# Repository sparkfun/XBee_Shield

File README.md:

XBee Shield
===========

<table class="table table-hover table-striped table-bordered">
  <tr align="center">
   <td></td>
   <td></td>
  </tr>
  <tr align="center">
    <td>XBee Shield [<a href="https://www.sparkfun.com/products/12847">WRL-12847</a>]</td>
    <td>SparkFun XBee Wireless Kit [<a href="https://www.sparkfun.com/products/13197">KIT-13197</a>]</td>
  </tr>
</table>

This shield mates directly with any dev board that has an Arduino standard footprint and equips it with the wireless
communication capabilities using the popular XBee modules. 

Repository Contents
-------------------
* **/Hardware** - All Eagle design files (.brd, .sch)
* **/Production** - Test bed files and production panel files

Documentation
--------------
* **[Exploring XBees and XCTU](https://learn.sparkfun.com/tutorials/exploring-xbees-and-xctu)** - Getting started with the XBee software and configuring XBees.
* **[Hookup Guide](https://learn.sparkfun.com/tutorials/xbee-shield-hookup-guide)** - Basic hookup guide for the XBee Shield for Arduinos.

Product Versions
----------------
* [WRL-12847](https://www.sparkfun.com/products/12847)- XBee Shield
* [KIT-13197](https://www.sparkfun.com/products/13197)- XBee Wireless Kit with XBee Series 1 Modules

Version History
---------------
* [v14](https://www.sparkfun.com/products/10854) Version 1.4. 

License Information
-------------------
License Information
-------------------

This product is _**open source**_! 

Please review the LICENSE.md file for license information. 

If you have any questions or concerns on licensing, please contact techsupport@sparkfun.com.

Distributed as-is; no warranty is given.

- Your friends at SparkFun.

_<COLLABORATION CREDIT>_

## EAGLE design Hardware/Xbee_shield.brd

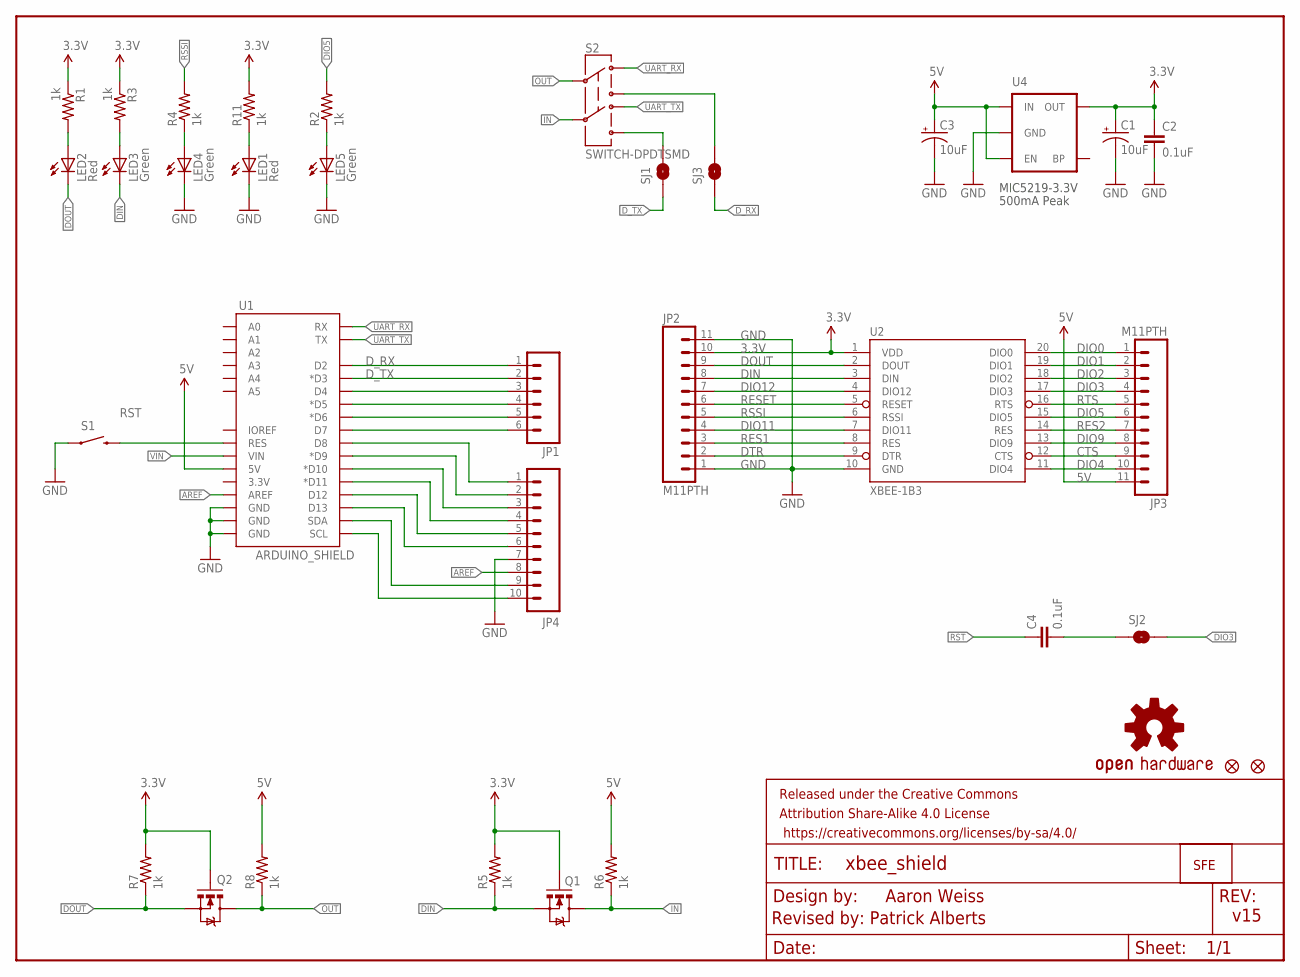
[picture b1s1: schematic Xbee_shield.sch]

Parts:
C1, C3: 10uF; EIA3216
C2, C4: 0.1uF; 0603-CAP
FRAME1: FRAME-LETTER; CREATIVE_COMMONS
JP1: M06SIP; 1X06
JP2, JP3: M11PTH; 1X11
JP4: M10"; 1X10
JP5, JP6: FIDUCIAL1X2; FIDUCIAL-1X2
JP7: LOGO-SFENEW; SFE-NEW-WEBLOGO
LED1, LED2: Red; LED-0603
LED3, LED4, LED5: Green; LED-0603
Q1, Q2: MOSFET-NCHANNELSMD; SOT23-3
R1, R2, R3, R4, R5, R6, R7, R8, R11: 1k; 0603-RES
S1: SWITCH-MOMENTARY-2SMD; TACTILE_SWITCH_SMD
S2: SWITCH-DPDTSMD; AYZ0202
SJ1: D_TX; SJ_2S
SJ2: SOLDERJUMPERTRACE; SJ_2S-TRACE
SJ3: D_RX; SJ_2S
U1: ARDUINO_SHIELD; UNO_R3_SHIELD
U2: XBEE-1B3; XBEE-SMD
U4: V_REG_LDOSMD; SOT23-5
U$8: OSHW-LOGOS; OSHW-LOGO-S

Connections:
3.3V: C1.A (+), C2.1, JP2.10, Q1.1 (G), Q2.1 (G), R1.1, R3.1, R5.2, R7.2, R11.2, U2.1 (VDD), U4.5 (OUT)
5V: C3.A (+), JP3.11, R6.2, R8.2, U1.5V, U4.1 (IN), U4.3 (EN)
AREF: JP4.8, U1.AREF
CTS: JP3.9, U2.12 (CTS)
DIN: JP2.8, LED3.C, Q1.2 (S), R5.1, U2.3 (DIN)
DIO0: JP3.1, U2.20 (DIO0)
DIO1: JP3.2, U2.19 (DIO1)
DIO2: JP3.3, U2.18 (DIO2)
DIO3: JP3.4, SJ2.2, U2.17 (DIO3)
DIO4: JP3.10, U2.11 (DIO4)
DIO5: JP3.6, R2.2, U2.15 (DIO5)
DIO9: JP3.8, U2.13 (DIO9)
DIO11: JP2.4, U2.7 (DIO11)
DIO12: JP2.7, U2.4 (DIO12)
DOUT: JP2.9, LED2.C, Q2.2 (S), R7.1, U2.2 (DOUT)
DTR: JP2.2, U2.9 (DTR)
D_RX: JP1.1, SJ3.1, U1.D2
D_TX: JP1.2, SJ1.1, U1.D3 (*D3)
GND: C1.C (-), C2.2, C3.C (-), JP2.1, JP2.11, JP4.7, LED1.C, LED4.C, LED5.C, S1.1, U1.GND@0 (GND), U1.GND@1 (GND), U1.GND@2 (GND), U2.10 (GND), U4.2 (GND)
IN: Q1.3 (D), R6.1, S2.5
unnamed: LED2.A, R1.2
unnamed: LED4.A, R4.1
unnamed: JP4.6, U1.D13
unnamed: LED3.A, R3.2
unnamed: C4.2, SJ2.1
unnamed: JP4.9, U1.SDA
unnamed: JP4.10, U1.SCL
unnamed: JP4.1, U1.D8
unnamed: JP4.2, U1.D9 (*D9)
unnamed: JP4.3, U1.D10 (*D10)
unnamed: LED1.A, R11.1
unnamed: JP4.4, U1.D11 (*D11)
unnamed: JP4.5, U1.D12
unnamed: LED5.A, R2.1
unnamed: S2.6, SJ1.2
unnamed: S2.3, SJ3.2
unnamed: JP1.3, U1.D4
unnamed: JP1.4, U1.D5 (*D5)
unnamed: JP1.5, U1.D6 (*D6)
unnamed: JP1.6, U1.D7
OUT: Q2.3 (D), R8.1, S2.2
RES1: JP2.3, U2.8 (RES)
RES2: JP3.7, U2.14 (RES)
RESET: JP2.6, U2.5 (RESET)
RSSI: JP2.5, R4.2, U2.6 (RSSI)
RST: C4.1, S1.3 (2), U1.RES
RTS: JP3.5, U2.16 (RTS)
UART_RX: S2.1, U1.RX
UART_TX: S2.4, U1.TX
VIN: U1.VIN

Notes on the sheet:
500mA Peak
MIC5219-3.3V
Aaron Weiss
v15
Revised by: Patrick Alberts

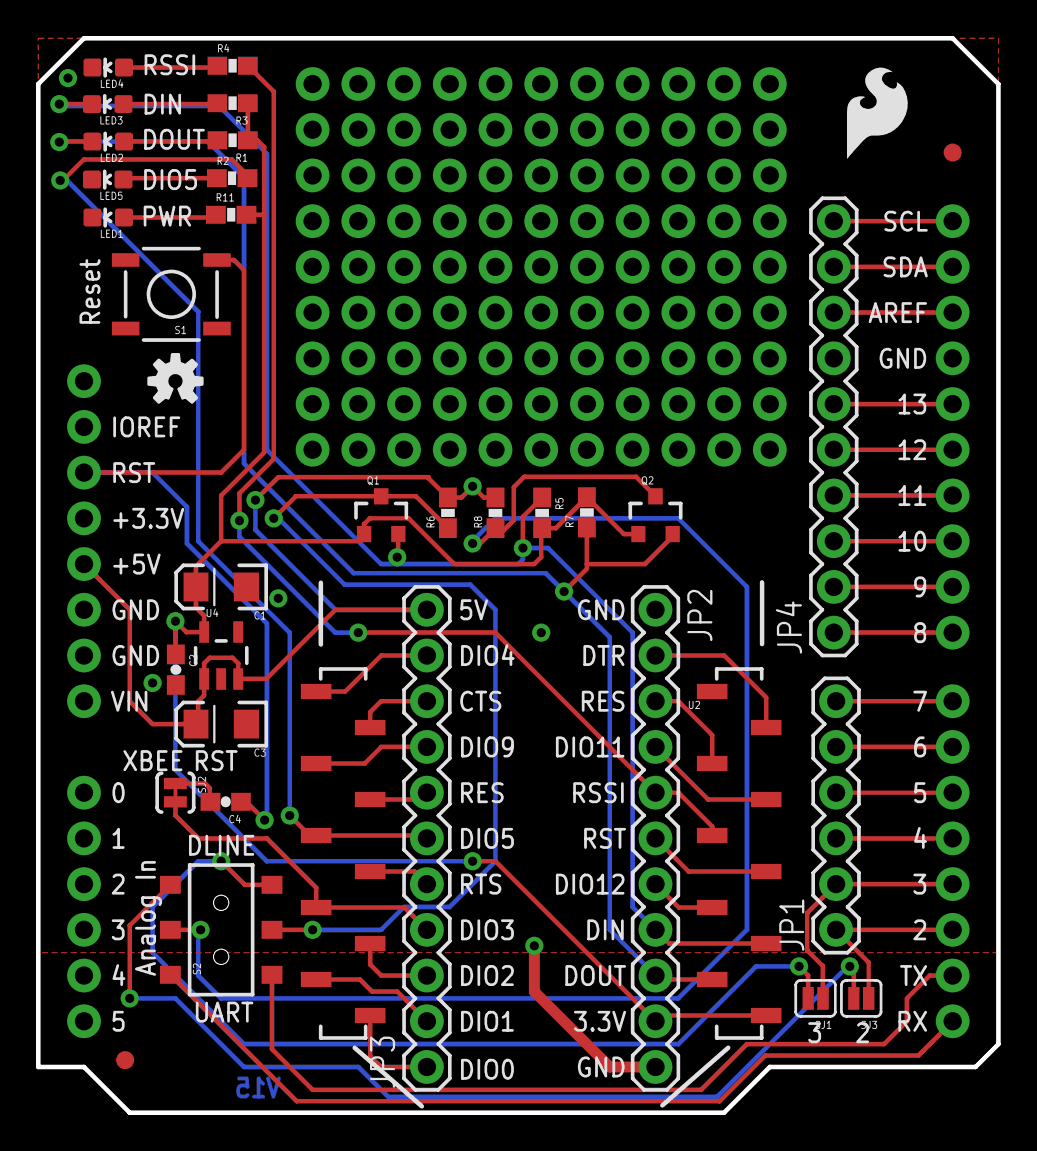
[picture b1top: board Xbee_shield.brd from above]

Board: 2 copper layers, 53.3 x 59.7 mm, 38 parts (1 on the bottom side), 49 nets.

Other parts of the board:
U$1: SFE_LOGO_FLAME_.2

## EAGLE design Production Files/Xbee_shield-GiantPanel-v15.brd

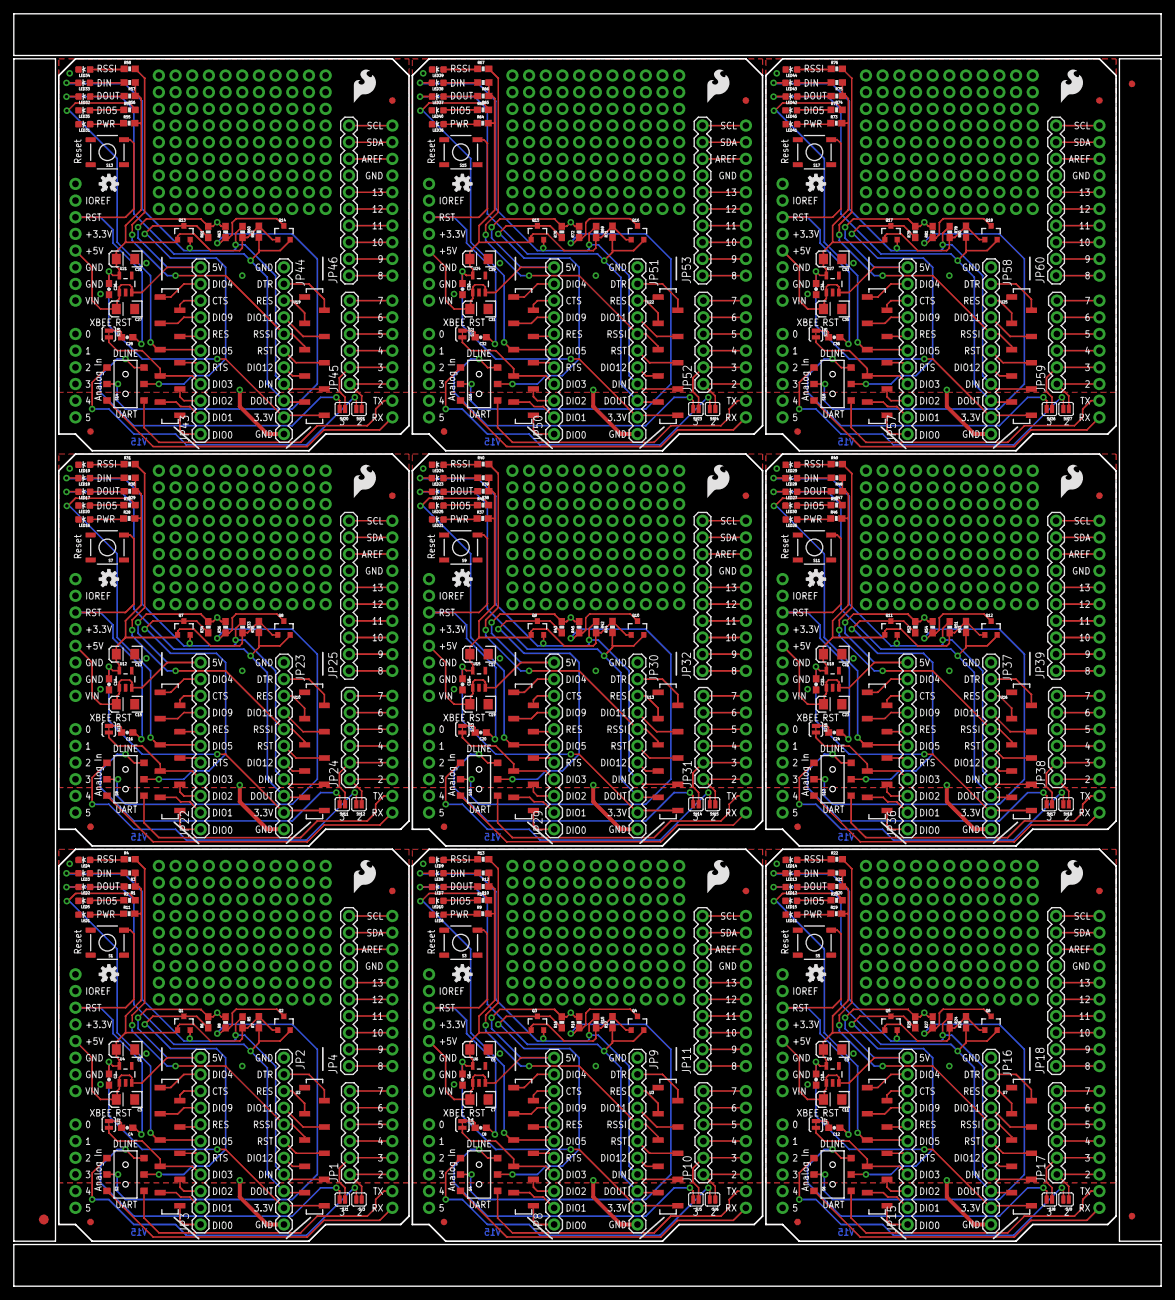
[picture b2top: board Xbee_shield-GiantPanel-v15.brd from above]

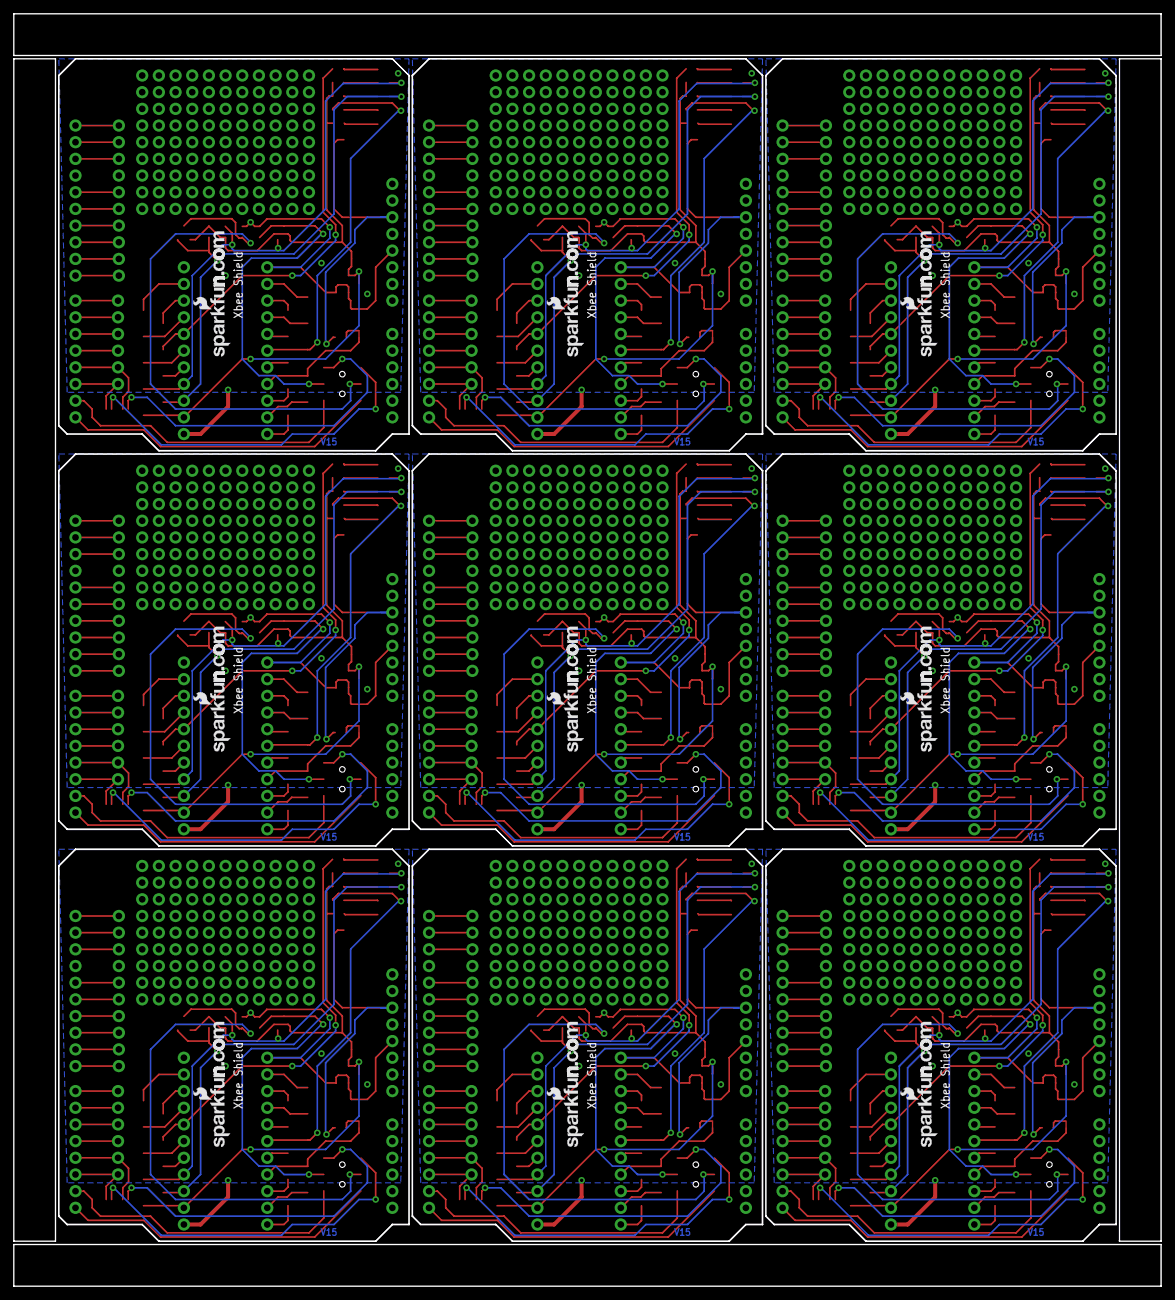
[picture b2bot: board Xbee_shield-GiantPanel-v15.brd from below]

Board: 2 copper layers, 174.7 x 193.8 mm, 336 parts (9 on the bottom side), 441 nets.

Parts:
C1, C3, C5, C7, C9, C11, C13, C15, C17, C19, C21, C23, C25, C27, C29, C31, C33, C35: 10uF; EIA3216
C2, C4, C6, C8, C10, C12, C14, C16, C18, C20, C22, C24, C26, C28, C30, C32, C34, C36: 0.1uF; 0603-CAP
E$1: FIDUCIAL-1.5X3
E$4, E$5: FIDUCIAL-1X2
JP1, JP10, JP17, JP24, JP31, JP38, JP45, JP52, JP59: 1X06
JP2, JP3, JP8, JP9, JP15, JP16, JP22, JP23, JP29, JP30, JP36, JP37, JP43, JP44, JP50, JP51, JP57, JP58: M11PTH; 1X11
JP4, JP11, JP18, JP25, JP32, JP39, JP46, JP53, JP60: 1X10
JP5, JP6, JP12, JP13, JP19, JP20, JP26, JP27, JP33, JP34, JP40, JP41, JP47, JP48, JP54, JP55, JP61, JP62: FIDUCIAL1X2; FIDUCIAL-1X2
JP7, JP14, JP21, JP28, JP35, JP42, JP49, JP56, JP63: LOGO-SFENEW; SFE-NEW-WEBLOGO
LED1, LED2, LED6, LED7, LED11, LED12, LED16, LED17, LED21, LED22, LED26, LED27, LED31, LED32, LED36, LED37, LED41, LED42: Red; LED-0603
LED3, LED4, LED5, LED8, LED9, LED10, LED13, LED14, LED15, LED18, LED19, LED20, LED23, LED24, LED25, LED28, LED29, LED30, LED33, LED34, LED35, LED38, LED39, LED40, LED43, LED44, LED45: Green; LED-0603
Q1, Q2, Q3, Q4, Q5, Q6, Q7, Q8, Q9, Q10, Q11, Q12, Q13, Q14, Q15, Q16, Q17, Q18: MOSFET-NCHANNELSMD; SOT23-3
R1, R2, R3, R4, R5, R6, R7, R8, R9, R10, R11, R12, R13, R14, R15, R16, R17, R18, R19, R20, R21, R22, R23, R24, R25, R26, R27, R28, R29, R30, R31, R32, R33, R34, R35, R36, R37, R38, R39, R40, R41, R42, R43, R44, R45, R46, R47, R48, R49, R50, R51, R52, R53, R54, R55, R56, R57, R58, R59, R60, R61, R62, R63, R64, R65, R66, R67, R68, R69, R70, R71, R72, R73, R74, R75, R76, R77, R78, R79, R80, R81: 1k; 0603-RES
S1, S3, S5, S7, S9, S11, S13, S15, S17: SWITCH-MOMENTARY-2SMD; TACTILE_SWITCH_SMD
S2, S4, S6, S8, S10, S12, S14, S16, S18: SWITCH-DPDTSMD; AYZ0202
SJ1, SJ5, SJ8, SJ11, SJ14, SJ17, SJ20, SJ23, SJ26: D_TX; SJ_2S
SJ2, SJ4, SJ7, SJ10, SJ13, SJ16, SJ19, SJ22, SJ25: SOLDERJUMPERTRACE; SJ_2S-TRACE
SJ3, SJ6, SJ9, SJ12, SJ15, SJ18, SJ21, SJ24, SJ27: D_RX; SJ_2S
U1, U5, U8, U11, U14, U17, U20, U23, U26: ARDUINO_SHIELD; UNO_R3_SHIELD
U2, U3, U7, U10, U13, U16, U19, U22, U25: XBEE-1B3; XBEE-SMD
U4, U6, U9, U12, U15, U18, U21, U24, U27: V_REG_LDOSMD; SOT23-5
U$1, U$3, U$5, U$7, U$10, U$12, U$14, U$16, U$18: SFE_LOGO_FLAME_.2
U$2, U$4, U$6, U$8, U$9, U$11, U$13, U$15, U$17: OSHW-LOGOS; OSHW-LOGO-S

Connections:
3.3V: C1.A, C2.1, JP2.10, Q1.1, Q2.1, R1.1, R3.1, R5.2, R7.2, R11.2, U2.1, U4.5
3.3V1: C5.A, C6.1, JP9.10, Q3.1, Q4.1, R9.2, R10.1, R12.1, R15.2, R17.2, U3.1, U6.5
3.3V2: C9.A, C10.1, JP16.10, Q5.1, Q6.1, R19.2, R20.1, R21.1, R24.2, R26.2, U7.1, U9.5
3.3V3: C13.A, C14.1, JP23.10, Q7.1, Q8.1, R28.2, R29.1, R30.1, R33.2, R35.2, U10.1, U12.5
3.3V4: C17.A, C18.1, JP30.10, Q9.1, Q10.1, R37.2, R38.1, R39.1, R42.2, R44.2, U13.1, U15.5
3.3V5: C21.A, C22.1, JP37.10, Q11.1, Q12.1, R46.2, R47.1, R48.1, R51.2, R53.2, U16.1, U18.5
3.3V6: C25.A, C26.1, JP44.10, Q13.1, Q14.1, R55.2, R56.1, R57.1, R60.2, R62.2, U19.1, U21.5
3.3V7: C29.A, C30.1, JP51.10, Q15.1, Q16.1, R64.2, R65.1, R66.1, R69.2, R71.2, U22.1, U24.5
3.3V8: C33.A, C34.1, JP58.10, Q17.1, Q18.1, R73.2, R74.1, R75.1, R78.2, R80.2, U25.1, U27.5
5V: C3.A, JP3.11, R6.2, R8.2, U1.5V, U4.1, U4.3
5V1: C7.A, JP8.11, R16.2, R18.2, U5.5V, U6.1, U6.3
5V2: C11.A, JP15.11, R25.2, R27.2, U8.5V, U9.1, U9.3
5V3: C15.A, JP22.11, R34.2, R36.2, U11.5V, U12.1, U12.3
5V4: C19.A, JP29.11, R43.2, R45.2, U14.5V, U15.1, U15.3
5V5: C23.A, JP36.11, R52.2, R54.2, U17.5V, U18.1, U18.3
5V6: C27.A, JP43.11, R61.2, R63.2, U20.5V, U21.1, U21.3
5V7: C31.A, JP50.11, R70.2, R72.2, U23.5V, U24.1, U24.3
5V8: C35.A, JP57.11, R79.2, R81.2, U26.5V, U27.1, U27.3
AREF: JP4.8, U1.AREF
AREF1: JP11.8, U5.AREF
AREF2: JP18.8, U8.AREF
AREF3: JP25.8, U11.AREF
AREF4: JP32.8, U14.AREF
AREF5: JP39.8, U17.AREF
AREF6: JP46.8, U20.AREF
AREF7: JP53.8, U23.AREF
AREF8: JP60.8, U26.AREF
CTS: JP3.9, U2.12
CTS1: JP8.9, U3.12
CTS2: JP15.9, U7.12
CTS3: JP22.9, U10.12
CTS4: JP29.9, U13.12
CTS5: JP36.9, U16.12
CTS6: JP43.9, U19.12
CTS7: JP50.9, U22.12
CTS8: JP57.9, U25.12
DIN: JP2.8, LED3.C, Q1.2, R5.1, U2.3
DIN1: JP9.8, LED8.C, Q3.2, R15.1, U3.3
DIN2: JP16.8, LED13.C, Q5.2, R24.1, U7.3
DIN3: JP23.8, LED18.C, Q7.2, R33.1, U10.3
DIN4: JP30.8, LED23.C, Q9.2, R42.1, U13.3
DIN5: JP37.8, LED28.C, Q11.2, R51.1, U16.3
DIN6: JP44.8, LED33.C, Q13.2, R60.1, U19.3
DIN7: JP51.8, LED38.C, Q15.2, R69.1, U22.3
DIN8: JP58.8, LED43.C, Q17.2, R78.1, U25.3
DIO0: JP3.1, U2.20
DIO1: JP3.2, U2.19
DIO2: JP3.3, U2.18
DIO3: JP3.4, SJ2.2, U2.17
DIO4: JP3.10, U2.11
DIO5: JP3.6, R2.2, U2.15
DIO6: JP8.10, U3.11
DIO7: JP8.8, U3.13
DIO8: JP8.6, R14.2, U3.15
DIO9: JP3.8, U2.13
DIO10: JP8.4, SJ4.2, U3.17
DIO11: JP2.4, U2.7
DIO12: JP2.7, U2.4
DIO13: JP8.3, U3.18
DIO14: JP8.2, U3.19
DIO15: JP8.1, U3.20
DIO16: JP9.4, U3.7
DIO17: JP9.7, U3.4
DIO18: JP15.10, U7.11
DIO19: JP15.8, U7.13
DIO20: JP15.6, R23.2, U7.15
DIO21: JP15.4, SJ7.2, U7.17
DIO22: JP15.3, U7.18
DIO23: JP15.2, U7.19
DIO24: JP15.1, U7.20
DIO25: JP16.4, U7.7
DIO26: JP16.7, U7.4
DIO27: JP22.10, U10.11
DIO28: JP22.8, U10.13
DIO29: JP22.6, R32.2, U10.15
DIO30: JP22.4, SJ10.2, U10.17
DIO31: JP22.3, U10.18
DIO32: JP22.2, U10.19
DIO33: JP22.1, U10.20
DIO34: JP23.4, U10.7
DIO35: JP23.7, U10.4
DIO36: JP29.10, U13.11
DIO37: JP29.8, U13.13
DIO38: JP29.6, R41.2, U13.15
DIO39: JP29.4, SJ13.2, U13.17
DIO40: JP29.3, U13.18
DIO41: JP29.2, U13.19
DIO42: JP29.1, U13.20
DIO43: JP30.4, U13.7
DIO44: JP30.7, U13.4
DIO45: JP36.10, U16.11
DIO46: JP36.8, U16.13
DIO47: JP36.6, R50.2, U16.15
DIO48: JP36.4, SJ16.2, U16.17
DIO49: JP36.3, U16.18
DIO50: JP36.2, U16.19
DIO51: JP36.1, U16.20
DIO52: JP37.4, U16.7
DIO53: JP37.7, U16.4
DIO54: JP43.10, U19.11
DIO55: JP43.8, U19.13
DIO56: JP43.6, R59.2, U19.15
DIO57: JP43.4, SJ19.2, U19.17
DIO58: JP43.3, U19.18
DIO59: JP43.2, U19.19
DIO60: JP43.1, U19.20
DIO61: JP44.4, U19.7
DIO62: JP44.7, U19.4
DIO63: JP50.10, U22.11
DIO64: JP50.8, U22.13
DIO65: JP50.6, R68.2, U22.15
DIO66: JP50.4, SJ22.2, U22.17
DIO67: JP50.3, U22.18
DIO68: JP50.2, U22.19
DIO69: JP50.1, U22.20
DIO70: JP51.4, U22.7
DIO71: JP51.7, U22.4
DIO72: JP57.10, U25.11
DIO73: JP57.8, U25.13
DIO74: JP57.6, R77.2, U25.15
DIO75: JP57.4, SJ25.2, U25.17
DIO76: JP57.3, U25.18
DIO77: JP57.2, U25.19
DIO78: JP57.1, U25.20
DIO79: JP58.4, U25.7
DIO80: JP58.7, U25.4
DOUT: JP2.9, LED2.C, Q2.2, R7.1, U2.2
DOUT1: JP9.9, LED7.C, Q4.2, R17.1, U3.2
DOUT2: JP16.9, LED12.C, Q6.2, R26.1, U7.2
DOUT3: JP23.9, LED17.C, Q8.2, R35.1, U10.2
DOUT4: JP30.9, LED22.C, Q10.2, R44.1, U13.2
DOUT5: JP37.9, LED27.C, Q12.2, R53.1, U16.2
DOUT6: JP44.9, LED32.C, Q14.2, R62.1, U19.2
DOUT7: JP51.9, LED37.C, Q16.2, R71.1, U22.2
DOUT8: JP58.9, LED42.C, Q18.2, R80.1, U25.2
DTR: JP2.2, U2.9
DTR1: JP9.2, U3.9
DTR2: JP16.2, U7.9
DTR3: JP23.2, U10.9
DTR4: JP30.2, U13.9
DTR5: JP37.2, U16.9
DTR6: JP44.2, U19.9
DTR7: JP51.2, U22.9
DTR8: JP58.2, U25.9
D_RX: JP1.1, SJ3.1, U1.D2
D_RX1: JP10.1, SJ6.1, U5.D2
D_RX2: JP17.1, SJ9.1, U8.D2
D_RX3: JP24.1, SJ12.1, U11.D2
D_RX4: JP31.1, SJ15.1, U14.D2
D_RX5: JP38.1, SJ18.1, U17.D2
D_RX6: JP45.1, SJ21.1, U20.D2
D_RX7: JP52.1, SJ24.1, U23.D2
D_RX8: JP59.1, SJ27.1, U26.D2
D_TX: JP1.2, SJ1.1, U1.D3
D_TX1: JP10.2, SJ5.1, U5.D3
D_TX2: JP17.2, SJ8.1, U8.D3
D_TX3: JP24.2, SJ11.1, U11.D3
D_TX4: JP31.2, SJ14.1, U14.D3
D_TX5: JP38.2, SJ17.1, U17.D3
D_TX6: JP45.2, SJ20.1, U20.D3
D_TX7: JP52.2, SJ23.1, U23.D3
D_TX8: JP59.2, SJ26.1, U26.D3
GND: C1.C, C2.2, C3.C, JP2.1, JP2.11, JP4.7, LED1.C, LED4.C, LED5.C, S1.1, U1.GND@0, U1.GND@1, U1.GND@2, U2.10, U4.2
GND1: C5.C, C6.2, C7.C, JP9.1, JP9.11, JP11.7, LED6.C, LED9.C, LED10.C, S3.1, U3.10, U5.GND@0, U5.GND@1, U5.GND@2, U6.2
GND2: C9.C, C10.2, C11.C, JP16.1, JP16.11, JP18.7, LED11.C, LED14.C, LED15.C, S5.1, U7.10, U8.GND@0, U8.GND@1, U8.GND@2, U9.2
GND3: C13.C, C14.2, C15.C, JP23.1, JP23.11, JP25.7, LED16.C, LED19.C, LED20.C, S7.1, U10.10, U11.GND@0, U11.GND@1, U11.GND@2, U12.2
GND4: C17.C, C18.2, C19.C, JP30.1, JP30.11, JP32.7, LED21.C, LED24.C, LED25.C, S9.1, U13.10, U14.GND@0, U14.GND@1, U14.GND@2, U15.2
GND5: C21.C, C22.2, C23.C, JP37.1, JP37.11, JP39.7, LED26.C, LED29.C, LED30.C, S11.1, U16.10, U17.GND@0, U17.GND@1, U17.GND@2, U18.2
GND6: C25.C, C26.2, C27.C, JP44.1, JP44.11, JP46.7, LED31.C, LED34.C, LED35.C, S13.1, U19.10, U20.GND@0, U20.GND@1, U20.GND@2, U21.2
GND7: C29.C, C30.2, C31.C, JP51.1, JP51.11, JP53.7, LED36.C, LED39.C, LED40.C, S15.1, U22.10, U23.GND@0, U23.GND@1, U23.GND@2, U24.2
GND8: C33.C, C34.2, C35.C, JP58.1, JP58.11, JP60.7, LED41.C, LED44.C, LED45.C, S17.1, U25.10, U26.GND@0, U26.GND@1, U26.GND@2, U27.2
IN: Q1.3, R6.1, S2.5
IN1: Q3.3, R16.1, S4.5
IN2: Q5.3, R25.1, S6.5
IN3: Q7.3, R34.1, S8.5
IN4: Q9.3, R43.1, S10.5
IN5: Q11.3, R52.1, S12.5
IN6: Q13.3, R61.1, S14.5
IN7: Q15.3, R70.1, S16.5
IN8: Q17.3, R79.1, S18.5
unnamed: LED2.A, R1.2
unnamed: LED4.A, R4.1
unnamed: JP4.6, U1.D13
unnamed: LED3.A, R3.2
unnamed: C4.2, SJ2.1
unnamed: JP4.9, U1.SDA
unnamed: JP4.10, U1.SCL
unnamed: LED6.A, R9.1
unnamed: LED7.A, R10.2
unnamed: LED8.A, R12.2
unnamed: LED9.A, R13.1
unnamed: C8.2, SJ4.1
unnamed: JP4.1, U1.D8
unnamed: JP4.2, U1.D9
unnamed: JP4.3, U1.D10
unnamed: LED1.A, R11.1
unnamed: JP4.4, U1.D11
unnamed: JP4.5, U1.D12
unnamed: LED5.A, R2.1
unnamed: S2.6, SJ1.2
unnamed: S2.3, SJ3.2
unnamed: JP1.3, U1.D4
unnamed: JP1.4, U1.D5
unnamed: JP1.5, U1.D6
unnamed: JP1.6, U1.D7
unnamed: LED10.A, R14.1
unnamed: S4.6, SJ5.2
unnamed: S4.3, SJ6.2
unnamed: JP10.3, U5.D4
unnamed: JP10.4, U5.D5
unnamed: JP10.5, U5.D6
unnamed: JP10.6, U5.D7
unnamed: JP11.1, U5.D8
unnamed: JP11.2, U5.D9
unnamed: JP11.3, U5.D10
unnamed: JP11.4, U5.D11
unnamed: JP11.5, U5.D12
unnamed: JP11.6, U5.D13
unnamed: JP11.9, U5.SDA
unnamed: JP11.10, U5.SCL
unnamed: LED11.A, R19.1
unnamed: LED12.A, R20.2
unnamed: LED13.A, R21.2
unnamed: LED14.A, R22.1
unnamed: C12.2, SJ7.1
unnamed: LED15.A, R23.1
unnamed: S6.6, SJ8.2
unnamed: S6.3, SJ9.2
unnamed: JP17.3, U8.D4
unnamed: JP17.4, U8.D5
unnamed: JP17.5, U8.D6
unnamed: JP17.6, U8.D7
unnamed: JP18.1, U8.D8
unnamed: JP18.2, U8.D9
unnamed: JP18.3, U8.D10
unnamed: JP18.4, U8.D11
unnamed: JP18.5, U8.D12
unnamed: JP18.6, U8.D13
unnamed: JP18.9, U8.SDA
unnamed: JP18.10, U8.SCL
unnamed: LED16.A, R28.1
unnamed: LED17.A, R29.2
unnamed: LED18.A, R30.2
unnamed: LED19.A, R31.1
unnamed: C16.2, SJ10.1
unnamed: LED20.A, R32.1
unnamed: S8.6, SJ11.2
unnamed: S8.3, SJ12.2
unnamed: JP24.3, U11.D4
unnamed: JP24.4, U11.D5
unnamed: JP24.5, U11.D6
unnamed: JP24.6, U11.D7
unnamed: JP25.1, U11.D8
unnamed: JP25.2, U11.D9
unnamed: JP25.3, U11.D10
unnamed: JP25.4, U11.D11
unnamed: JP25.5, U11.D12
unnamed: JP25.6, U11.D13
unnamed: JP25.9, U11.SDA
unnamed: JP25.10, U11.SCL
unnamed: LED21.A, R37.1
unnamed: LED22.A, R38.2
unnamed: LED23.A, R39.2
unnamed: LED24.A, R40.1
unnamed: C20.2, SJ13.1
unnamed: LED25.A, R41.1
unnamed: S10.6, SJ14.2
unnamed: S10.3, SJ15.2
unnamed: JP31.3, U14.D4
unnamed: JP31.4, U14.D5
unnamed: JP31.5, U14.D6
unnamed: JP31.6, U14.D7
unnamed: JP32.1, U14.D8
unnamed: JP32.2, U14.D9
unnamed: JP32.3, U14.D10
unnamed: JP32.4, U14.D11
unnamed: JP32.5, U14.D12
unnamed: JP32.6, U14.D13
unnamed: JP32.9, U14.SDA
unnamed: JP32.10, U14.SCL
unnamed: LED26.A, R46.1
unnamed: LED27.A, R47.2
unnamed: LED28.A, R48.2
unnamed: LED29.A, R49.1
unnamed: C24.2, SJ16.1
unnamed: LED30.A, R50.1
unnamed: S12.6, SJ17.2
unnamed: S12.3, SJ18.2
unnamed: JP38.3, U17.D4
unnamed: JP38.4, U17.D5
unnamed: JP38.5, U17.D6
unnamed: JP38.6, U17.D7
unnamed: JP39.1, U17.D8
unnamed: JP39.2, U17.D9
unnamed: JP39.3, U17.D10
unnamed: JP39.4, U17.D11
unnamed: JP39.5, U17.D12
unnamed: JP39.6, U17.D13
unnamed: JP39.9, U17.SDA
unnamed: JP39.10, U17.SCL
unnamed: LED31.A, R55.1
unnamed: LED32.A, R56.2
unnamed: LED33.A, R57.2
unnamed: LED34.A, R58.1
unnamed: C28.2, SJ19.1
unnamed: LED35.A, R59.1
unnamed: S14.6, SJ20.2
unnamed: S14.3, SJ21.2
unnamed: JP45.3, U20.D4
unnamed: JP45.4, U20.D5
unnamed: JP45.5, U20.D6
unnamed: JP45.6, U20.D7
unnamed: JP46.1, U20.D8
unnamed: JP46.2, U20.D9
unnamed: JP46.3, U20.D10
unnamed: JP46.4, U20.D11
unnamed: JP46.5, U20.D12
unnamed: JP46.6, U20.D13
unnamed: JP46.9, U20.SDA
unnamed: JP46.10, U20.SCL
unnamed: LED36.A, R64.1
unnamed: LED37.A, R65.2
unnamed: LED38.A, R66.2
unnamed: LED39.A, R67.1
unnamed: C32.2, SJ22.1
unnamed: LED40.A, R68.1
unnamed: S16.6, SJ23.2
unnamed: S16.3, SJ24.2
unnamed: JP52.3, U23.D4
unnamed: JP52.4, U23.D5
unnamed: JP52.5, U23.D6
unnamed: JP52.6, U23.D7
unnamed: JP53.1, U23.D8
unnamed: JP53.2, U23.D9
unnamed: JP53.3, U23.D10
unnamed: JP53.4, U23.D11
unnamed: JP53.5, U23.D12
unnamed: JP53.6, U23.D13
unnamed: JP53.9, U23.SDA
unnamed: JP53.10, U23.SCL
unnamed: LED41.A, R73.1
unnamed: LED42.A, R74.2
unnamed: LED43.A, R75.2
unnamed: LED44.A, R76.1
unnamed: C36.2, SJ25.1
unnamed: LED45.A, R77.1
unnamed: S18.6, SJ26.2
unnamed: S18.3, SJ27.2
unnamed: JP59.3, U26.D4
unnamed: JP59.4, U26.D5
unnamed: JP59.5, U26.D6
unnamed: JP59.6, U26.D7
unnamed: JP60.1, U26.D8
unnamed: JP60.2, U26.D9
unnamed: JP60.3, U26.D10
unnamed: JP60.4, U26.D11
unnamed: JP60.5, U26.D12
unnamed: JP60.6, U26.D13
unnamed: JP60.9, U26.SDA
unnamed: JP60.10, U26.SCL
OUT: Q2.3, R8.1, S2.2
OUT1: Q4.3, R18.1, S4.2
OUT2: Q6.3, R27.1, S6.2
OUT3: Q8.3, R36.1, S8.2
OUT4: Q10.3, R45.1, S10.2
OUT5: Q12.3, R54.1, S12.2
OUT6: Q14.3, R63.1, S14.2
OUT7: Q16.3, R72.1, S16.2
OUT8: Q18.3, R81.1, S18.2
RES1: JP2.3, U2.8
RES2: JP3.7, U2.14
RES3: JP9.3, U3.8
RES4: JP8.7, U3.14
RES5: JP16.3, U7.8
RES6: JP15.7, U7.14
RES7: JP23.3, U10.8
RES8: JP22.7, U10.14
RES9: JP30.3, U13.8
RES10: JP29.7, U13.14
RES11: JP37.3, U16.8
RES12: JP36.7, U16.14
RES13: JP44.3, U19.8
RES14: JP43.7, U19.14
RES15: JP51.3, U22.8
RES16: JP50.7, U22.14
RES17: JP58.3, U25.8
RES18: JP57.7, U25.14
RESET: JP2.6, U2.5
RESET1: JP9.6, U3.5
RESET2: JP16.6, U7.5
RESET3: JP23.6, U10.5
RESET4: JP30.6, U13.5
RESET5: JP37.6, U16.5
RESET6: JP44.6, U19.5
RESET7: JP51.6, U22.5
RESET8: JP58.6, U25.5
RSSI: JP2.5, R4.2, U2.6
RSSI1: JP9.5, R13.2, U3.6
RSSI2: JP16.5, R22.2, U7.6
RSSI3: JP23.5, R31.2, U10.6
RSSI4: JP30.5, R40.2, U13.6
RSSI5: JP37.5, R49.2, U16.6
RSSI6: JP44.5, R58.2, U19.6
RSSI7: JP51.5, R67.2, U22.6
RSSI8: JP58.5, R76.2, U25.6
RST: C4.1, S1.3, U1.RES
RST1: C8.1, S3.3, U5.RES
RST2: C12.1, S5.3, U8.RES
RST3: C16.1, S7.3, U11.RES
RST4: C20.1, S9.3, U14.RES
RST5: C24.1, S11.3, U17.RES
RST6: C28.1, S13.3, U20.RES
RST7: C32.1, S15.3, U23.RES
RST8: C36.1, S17.3, U26.RES
RTS: JP3.5, U2.16
RTS1: JP8.5, U3.16
RTS2: JP15.5, U7.16
RTS3: JP22.5, U10.16
RTS4: JP29.5, U13.16
RTS5: JP36.5, U16.16
RTS6: JP43.5, U19.16
RTS7: JP50.5, U22.16
RTS8: JP57.5, U25.16
UART_RX: S2.1, U1.RX
UART_RX1: S4.1, U5.RX
UART_RX2: S6.1, U8.RX
UART_RX3: S8.1, U11.RX
UART_RX4: S10.1, U14.RX
UART_RX5: S12.1, U17.RX
UART_RX6: S14.1, U20.RX
UART_RX7: S16.1, U23.RX
UART_RX8: S18.1, U26.RX
UART_TX: S2.4, U1.TX
UART_TX1: S4.4, U5.TX
UART_TX2: S6.4, U8.TX
UART_TX3: S8.4, U11.TX
UART_TX4: S10.4, U14.TX
UART_TX5: S12.4, U17.TX
UART_TX6: S14.4, U20.TX
UART_TX7: S16.4, U23.TX
UART_TX8: S18.4, U26.TX

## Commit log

2013-09-23 Initial Commit
    Initial commit with Readme and Gitignore
2014-02-06 Updating README
2014-03-13 Updates to res/caps/r3 sheild, trace re routes
2014-03-13 Fixed LED's/Silk
2014-03-14 Sch work
2014-03-20 Changes to Silk/SCH
2014-03-31 Update README.md
    Fixing name typos.
2014-04-01 Updated Silk
    Fixed spelling error
2014-04-05 created v15 giant panel
2014-07-28 Updating README for new version

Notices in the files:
parts and their libraries:
SparkFun-DiscreteSemi: Licensing: CC v3.0 Share-Alike You are welcome to use this library for commercial purposes.
SparkFun-Aesthetics: Released under the Creative Commons Attribution Share-Alike 4.0 License
SparkFun-Aesthetics: https://creativecommons.org/licenses/by-sa/4.0
